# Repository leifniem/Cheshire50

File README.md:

# Cheshire 50 - WIP!!!
#### 50% Alice / Arisu style keyboard

---

**DISCLAIMER: This is my first keyboard design, so things might be a little odd**

# Features
 - Gasket Mount
 - Daughterboard with USB-C
 - Arrow Cluster
 - optional Split Spacebars
 - optional Split Backspace
 - up to 52 keys
 - Open Source (duh)

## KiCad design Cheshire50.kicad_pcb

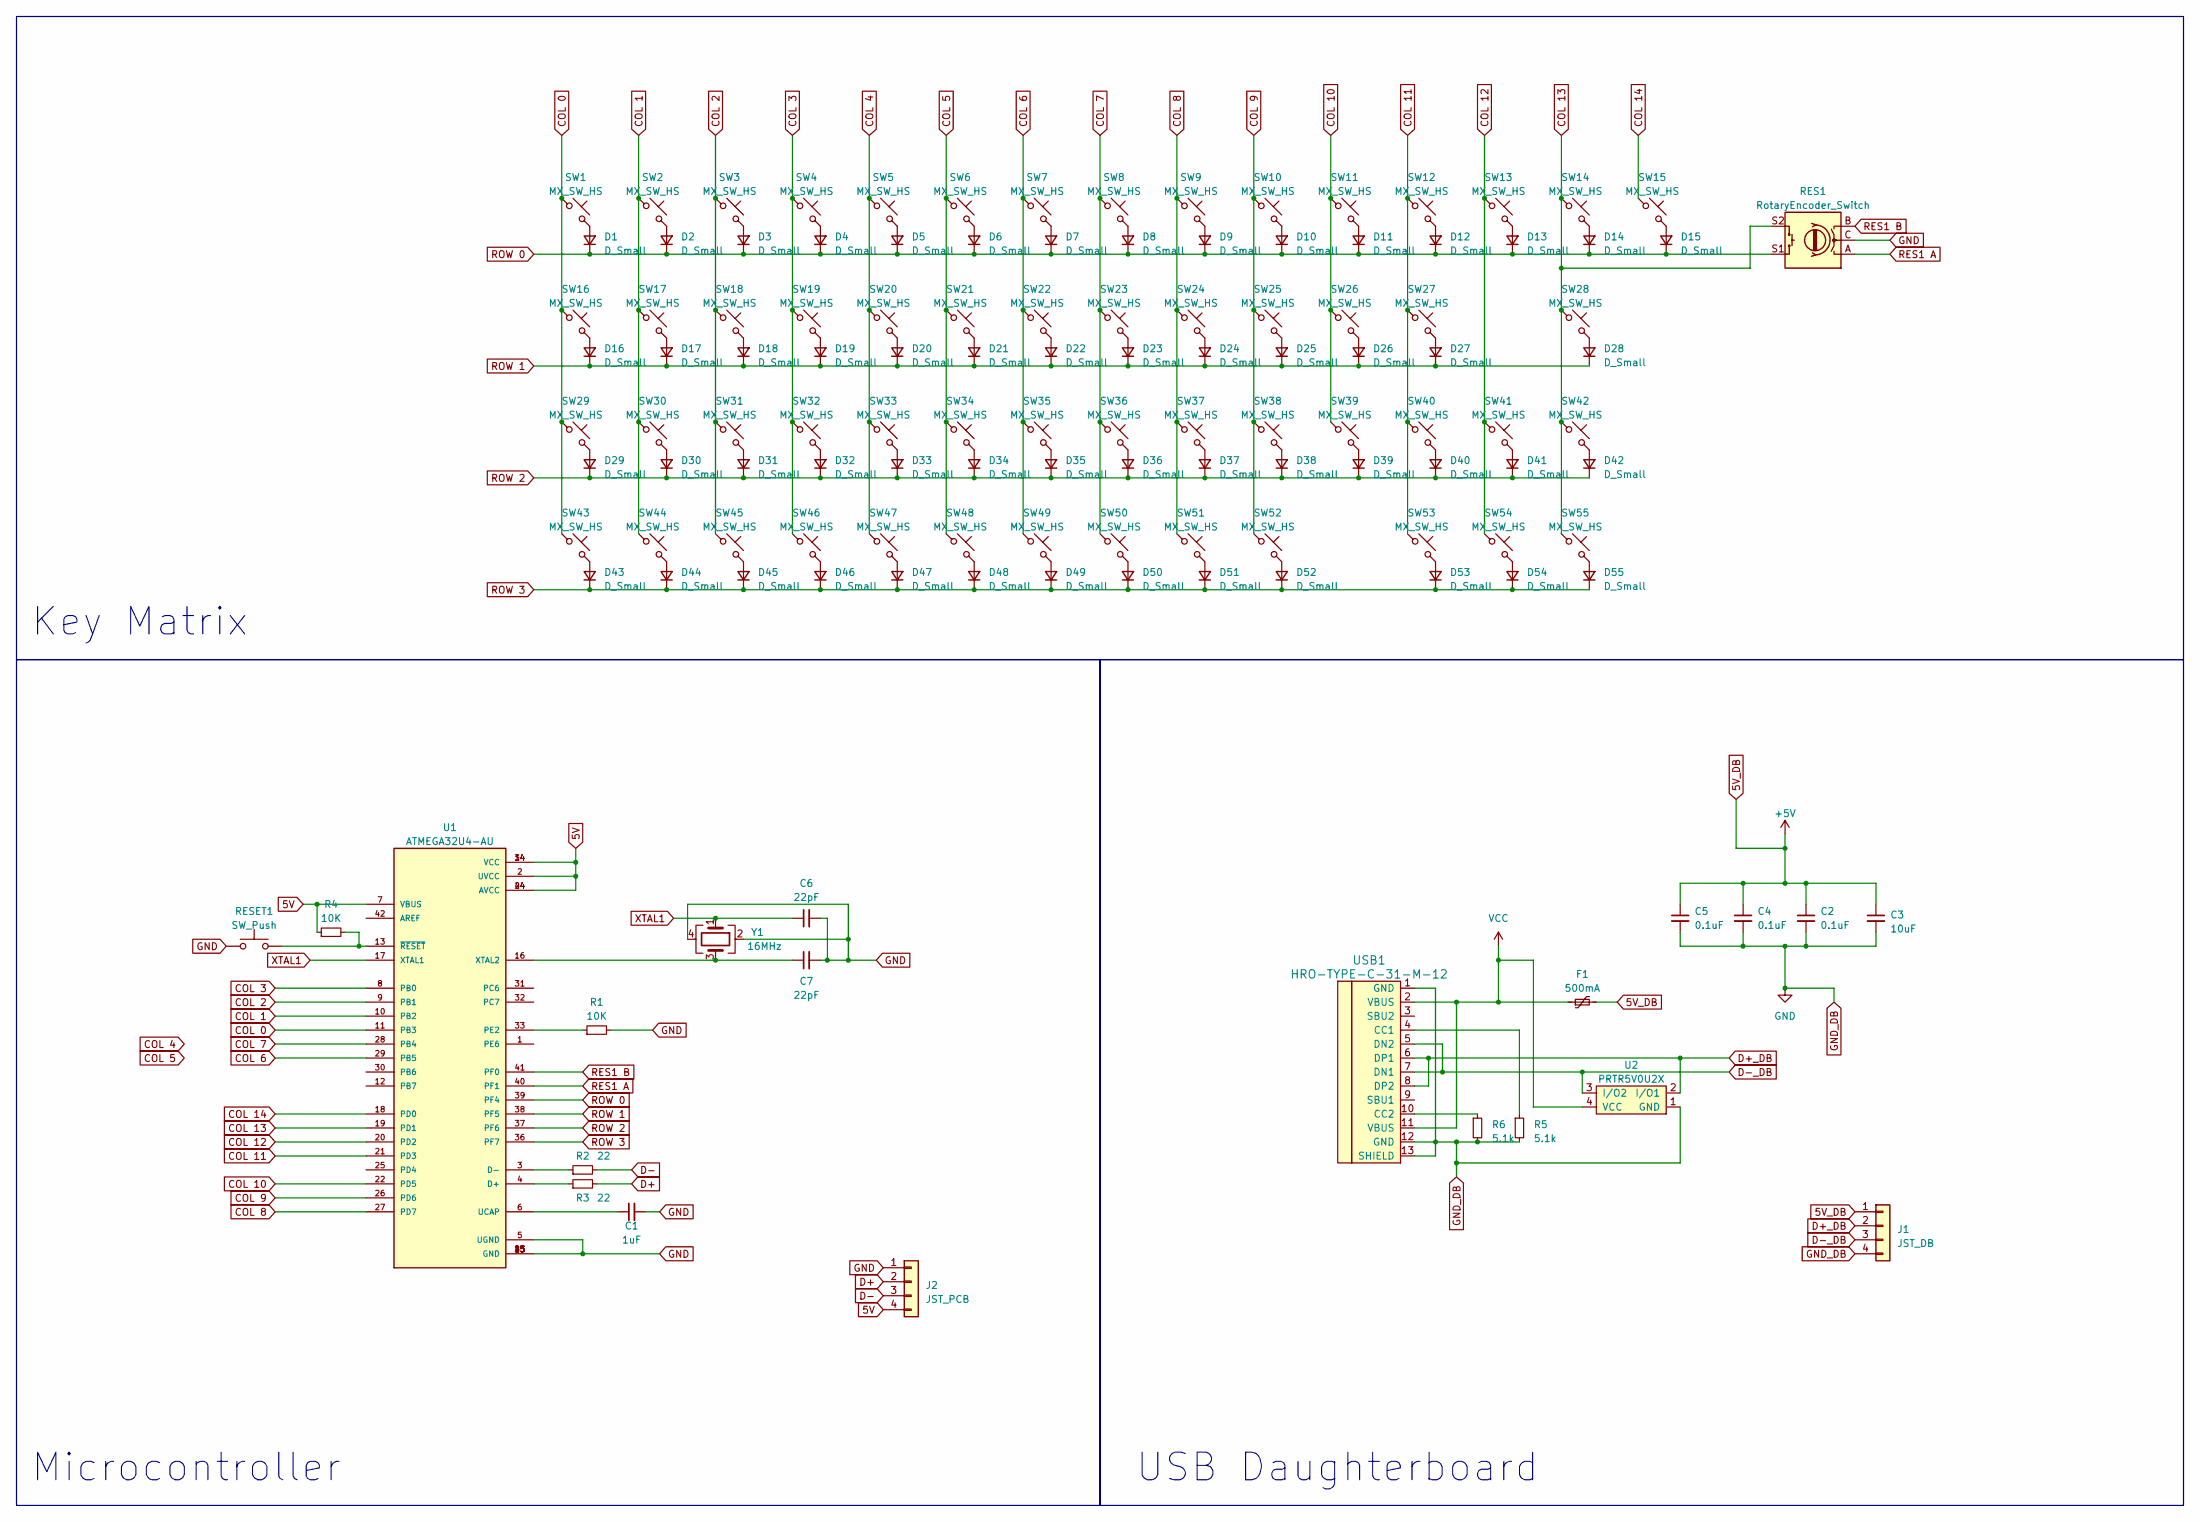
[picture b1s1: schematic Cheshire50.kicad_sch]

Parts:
C1: 1uF; C_0805_2012Metric
C2, C4, C5: 0.1uF; C_0805_2012Metric
C3: 10uF; C_0805_2012Metric
C6, C7: 22pF; C_0805_2012Metric
D1, D2, D3, D4, D5, D6, D7, D8, D9, D10, D11, D12, D13, D14, D15, D16, D17, D18, D19, D20, D21, D22, D23, D24, D25, D26, D27, D28, D29, D30, D31, D32, D33, D34, D35, D36, D37, D38, D39, D40, D41, D42, D43, D44, D45, D46, D47, D48, D49, D50, D51, D52, D53, D54, D55: D_Small; Diode-Hybrid-Back
F1: 500mA; Fuse_1206_3216Metric
J1: JST_DB; JST_PH_B4B-PH-SM4-TB_1x04-1MP_P2.00mm_Vertical
J2: JST_PCB; JST_PH_B4B-PH-SM4-TB_1x04-1MP_P2.00mm_Vertical
R1, R4: 10K; R_0805_2012Metric
R2, R3: 22; R_0805_2012Metric
R5, R6: 5.1k; R_0805_2012Metric
RES1: RotaryEncoder_Switch; RotaryEncoder_EC11
RESET1: SW_Push; SKQG-1155865
SW1, SW2, SW3, SW4, SW5, SW6, SW7, SW8, SW9, SW10, SW11, SW12, SW13, SW14, SW15, SW16, SW17, SW18, SW19, SW20, SW21, SW22, SW23, SW24, SW25, SW26, SW27, SW28, SW29, SW30, SW31, SW32, SW33, SW34, SW35, SW36, SW37, SW38, SW39, SW40, SW41, SW42, SW43, SW44, SW45, SW46, SW47, SW48, SW49, SW50, SW51, SW52, SW53, SW54, SW55: MX_SW_HS; SW_MX_HS_1u
U1: ATMEGA32U4-AU
U2: PRTR5V0U2X; SOT143B
USB1: HRO-TYPE-C-31-M-12; HRO-TYPE-C-31-M-12-Assembly
Y1: 16MHz; Crystal_SMD_3225-4Pin_3.2x2.5mm

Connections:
5V: J2.4, R4.1, U1.2 (UVCC), U1.7 (VBUS), U1.14 (VCC), U1.24 (AVCC), U1.34 (VCC), U1.44 (AVCC)
5V_DB: C2.1, C3.1, C4.1, C5.1, F1.2, J1.1
COL 0: SW1.1, SW16.1, SW29.1, SW43.1, U1.11 (PB3)
COL 1: SW2.1, SW17.1, SW30.1, SW44.1, U1.10 (PB2)
COL 2: SW3.1, SW18.1, SW31.1, SW45.1, U1.9 (PB1)
COL 3: SW4.1, SW19.1, SW32.1, SW46.1, U1.8 (PB0)
COL 4: SW5.1, SW20.1, SW33.1, SW47.1
COL 5: SW6.1, SW21.1, SW34.1, SW48.1
COL 6: SW7.1, SW22.1, SW35.1, SW49.1, U1.29 (PB5)
COL 7: SW8.1, SW23.1, SW36.1, SW50.1, U1.28 (PB4)
COL 8: SW9.1, SW24.1, SW37.1, SW51.1, U1.27 (PD7)
COL 9: SW10.1, SW25.1, SW38.1, SW52.1, U1.26 (PD6)
COL 10: SW11.1, SW26.1, SW39.1, U1.22 (PD5)
COL 11: SW12.1, SW27.1, SW40.1, SW53.1, U1.21 (PD3)
COL 12: SW13.1, SW41.1, SW54.1, U1.20 (PD2)
COL 13: RES1.S2, SW14.1, SW28.1, SW42.1, SW55.1, U1.19 (PD1)
COL 14: SW15.1, U1.18 (PD0)
D+: J2.2, R3.2
D+_DB: J1.2, U2.2 (I/O1), USB1.6 (DP1), USB1.8 (DP2)
D-: J2.3, R2.2
D-_DB: J1.3, U2.3 (I/O2), USB1.5 (DN2), USB1.7 (DN1)
GND: C1.2, C2.2, C3.2, C4.2, C5.2, C6.2, C7.2, J1.4, J2.1, R1.2, R5.2, R6.2, RES1.C, RESET1.1, U1.5 (UGND), U1.15 (GND), U1.23 (GND), U1.35 (GND), U1.43 (GND), U2.1 (GND), USB1.1 (GND), USB1.12 (GND), USB1.13 (SHIELD), Y1.2, Y1.4
unnamed: D1.2 (A), SW1.2
unnamed: D2.2 (A), SW2.2
unnamed: D3.2 (A), SW3.2
unnamed: D4.2 (A), SW4.2
unnamed: D5.2 (A), SW5.2
unnamed: D6.2 (A), SW6.2
unnamed: D7.2 (A), SW7.2
unnamed: D8.2 (A), SW8.2
unnamed: D9.2 (A), SW9.2
unnamed: D10.2 (A), SW10.2
unnamed: D11.2 (A), SW11.2
unnamed: D12.2 (A), SW12.2
unnamed: D13.2 (A), SW13.2
unnamed: D14.2 (A), SW14.2
unnamed: D15.2 (A), SW15.2
unnamed: D16.2 (A), SW16.2
unnamed: D17.2 (A), SW17.2
unnamed: D18.2 (A), SW18.2
unnamed: D19.2 (A), SW19.2
unnamed: D20.2 (A), SW20.2
unnamed: D21.2 (A), SW21.2
unnamed: D22.2 (A), SW22.2
unnamed: D23.2 (A), SW23.2
unnamed: D24.2 (A), SW24.2
unnamed: D25.2 (A), SW25.2
unnamed: D26.2 (A), SW26.2
unnamed: D27.2 (A), SW27.2
unnamed: D28.2 (A), SW28.2
unnamed: D29.2 (A), SW29.2
unnamed: D30.2 (A), SW30.2
unnamed: D31.2 (A), SW31.2
unnamed: D32.2 (A), SW32.2
unnamed: D33.2 (A), SW33.2
unnamed: D34.2 (A), SW34.2
unnamed: D35.2 (A), SW35.2
unnamed: D36.2 (A), SW36.2
unnamed: D37.2 (A), SW37.2
unnamed: D38.2 (A), SW38.2
unnamed: D39.2 (A), SW39.2
unnamed: D40.2 (A), SW40.2
unnamed: D41.2 (A), SW41.2
unnamed: D42.2 (A), SW42.2
unnamed: D43.2 (A), SW43.2
unnamed: D44.2 (A), SW44.2
unnamed: D45.2 (A), SW45.2
unnamed: D46.2 (A), SW46.2
unnamed: D47.2 (A), SW47.2
unnamed: D48.2 (A), SW48.2
unnamed: D49.2 (A), SW49.2
unnamed: D50.2 (A), SW50.2
unnamed: D51.2 (A), SW51.2
unnamed: D52.2 (A), SW52.2
unnamed: D53.2 (A), SW53.2
unnamed: D54.2 (A), SW54.2
unnamed: D55.2 (A), SW55.2
unnamed: R3.1, U1.4 (D+)
unnamed: R2.1, U1.3 (D-)
unnamed: R1.1, U1.33 (PE2)
unnamed: C1.1, U1.6 (UCAP)
unnamed: C7.1, U1.16 (XTAL2), Y1.3
unnamed: R4.2, RESET1.2, U1.13 (~RESET)
unnamed: R5.1, USB1.4 (CC1)
unnamed: R6.1, USB1.10 (CC2)
RES1 A: RES1.A, U1.40 (PF1)
RES1 B: RES1.B, U1.41 (PF0)
ROW 0: D1.1 (K), D2.1 (K), D3.1 (K), D4.1 (K), D5.1 (K), D6.1 (K), D7.1 (K), D8.1 (K), D9.1 (K), D10.1 (K), D11.1 (K), D12.1 (K), D13.1 (K), D14.1 (K), D15.1 (K), RES1.S1, U1.39 (PF4)
ROW 1: D16.1 (K), D17.1 (K), D18.1 (K), D19.1 (K), D20.1 (K), D21.1 (K), D22.1 (K), D23.1 (K), D24.1 (K), D25.1 (K), D26.1 (K), D27.1 (K), D28.1 (K), U1.38 (PF5)
ROW 2: D29.1 (K), D30.1 (K), D31.1 (K), D32.1 (K), D33.1 (K), D34.1 (K), D35.1 (K), D36.1 (K), D37.1 (K), D38.1 (K), D39.1 (K), D40.1 (K), D41.1 (K), D42.1 (K), U1.37 (PF6)
ROW 3: D43.1 (K), D44.1 (K), D45.1 (K), D46.1 (K), D47.1 (K), D48.1 (K), D49.1 (K), D50.1 (K), D51.1 (K), D52.1 (K), D53.1 (K), D54.1 (K), D55.1 (K), U1.36 (PF7)
VCC: F1.1, U2.4 (VCC), USB1.2 (VBUS), USB1.11 (VBUS)
XTAL1: C6.1, U1.17 (XTAL1), Y1.1

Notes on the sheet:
Microcontroller
Key Matrix
USB Daughterboard

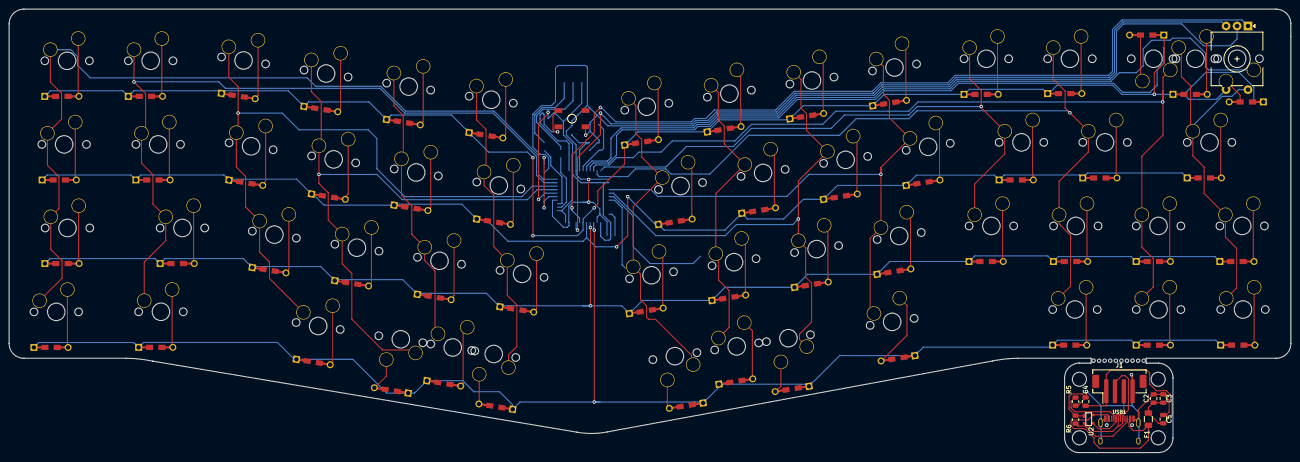
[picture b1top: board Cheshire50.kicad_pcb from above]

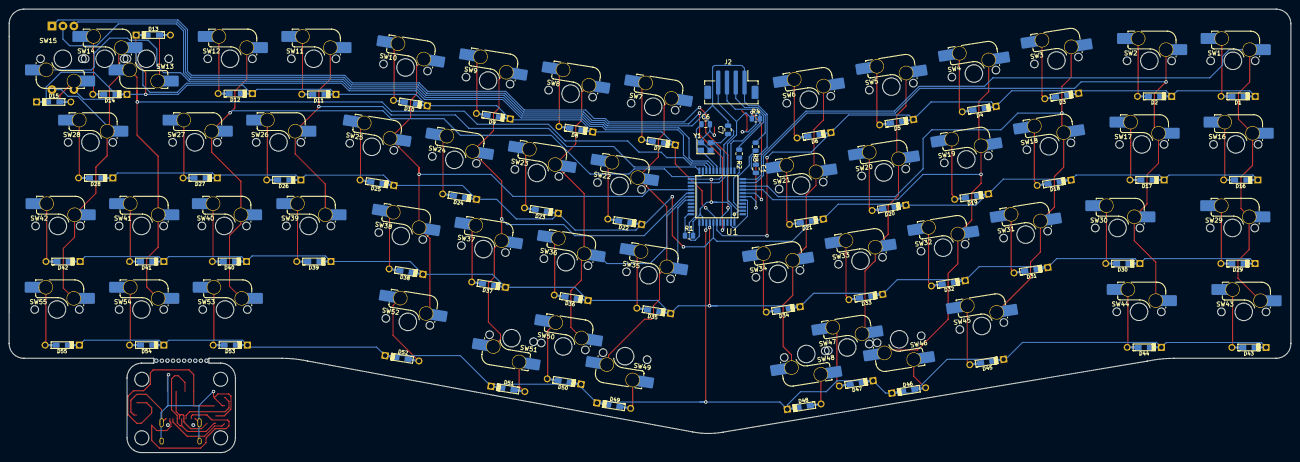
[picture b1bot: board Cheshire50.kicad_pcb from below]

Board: 2 copper layers, 292.1 x 101.1 mm, 132 parts (120 on the bottom side), 93 nets.

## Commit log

2023-03-26 init
2023-03-26 layout image
2023-03-26 readme update and remove old layouts
2023-03-27 new routing and logo
2023-04-01 rewire to reduce pcb width ... by 5mm
2023-04-07 rerouting, moved daughterboard to bottom to save space
